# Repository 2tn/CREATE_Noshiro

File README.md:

# CREATE_Noshiro
2015年8月の能代宇宙イベントで打ち上げたCREATEのロケットに搭載したアビオニクス、「われのロガー2」のプログラム及び発注基板データ。

基板にはLPC1114とATtiny2313の二つのマイコンが搭載されている。
搭載したパーツは
- LPC1114FBD48 (メインマイコン)
- ATtiny2313-20MU (サブマイコン)
- MPU9250 (9軸センサー)
- ADXL375 (3軸大加速度センサー)
- MPL3115A2 (気圧センサー)
- BQ25071 (LiFePo充電制御チップ)
- TPS63001DRCTF4 (3.3V DC/DCコンバーター)
- LTC3872 (12V DC/DCコンバーター)
- TWE-strong (ダウンリンク用無線機器)

っていう感じ。結局のところ時間切れでATtiny2313は動かせなかった…

## われのロガー2_ATtiny2313
UARTでGPSを読んで、SPIでデータをLPC1114に渡すプログラム
## われのロガー2_LPC1114
LPC1114がGPS以外のデータ取得・SDカードへの書き込み・パラシュート開放指令を行うプログラム
## 基板
作った基板データ、Elecrowで発注した。

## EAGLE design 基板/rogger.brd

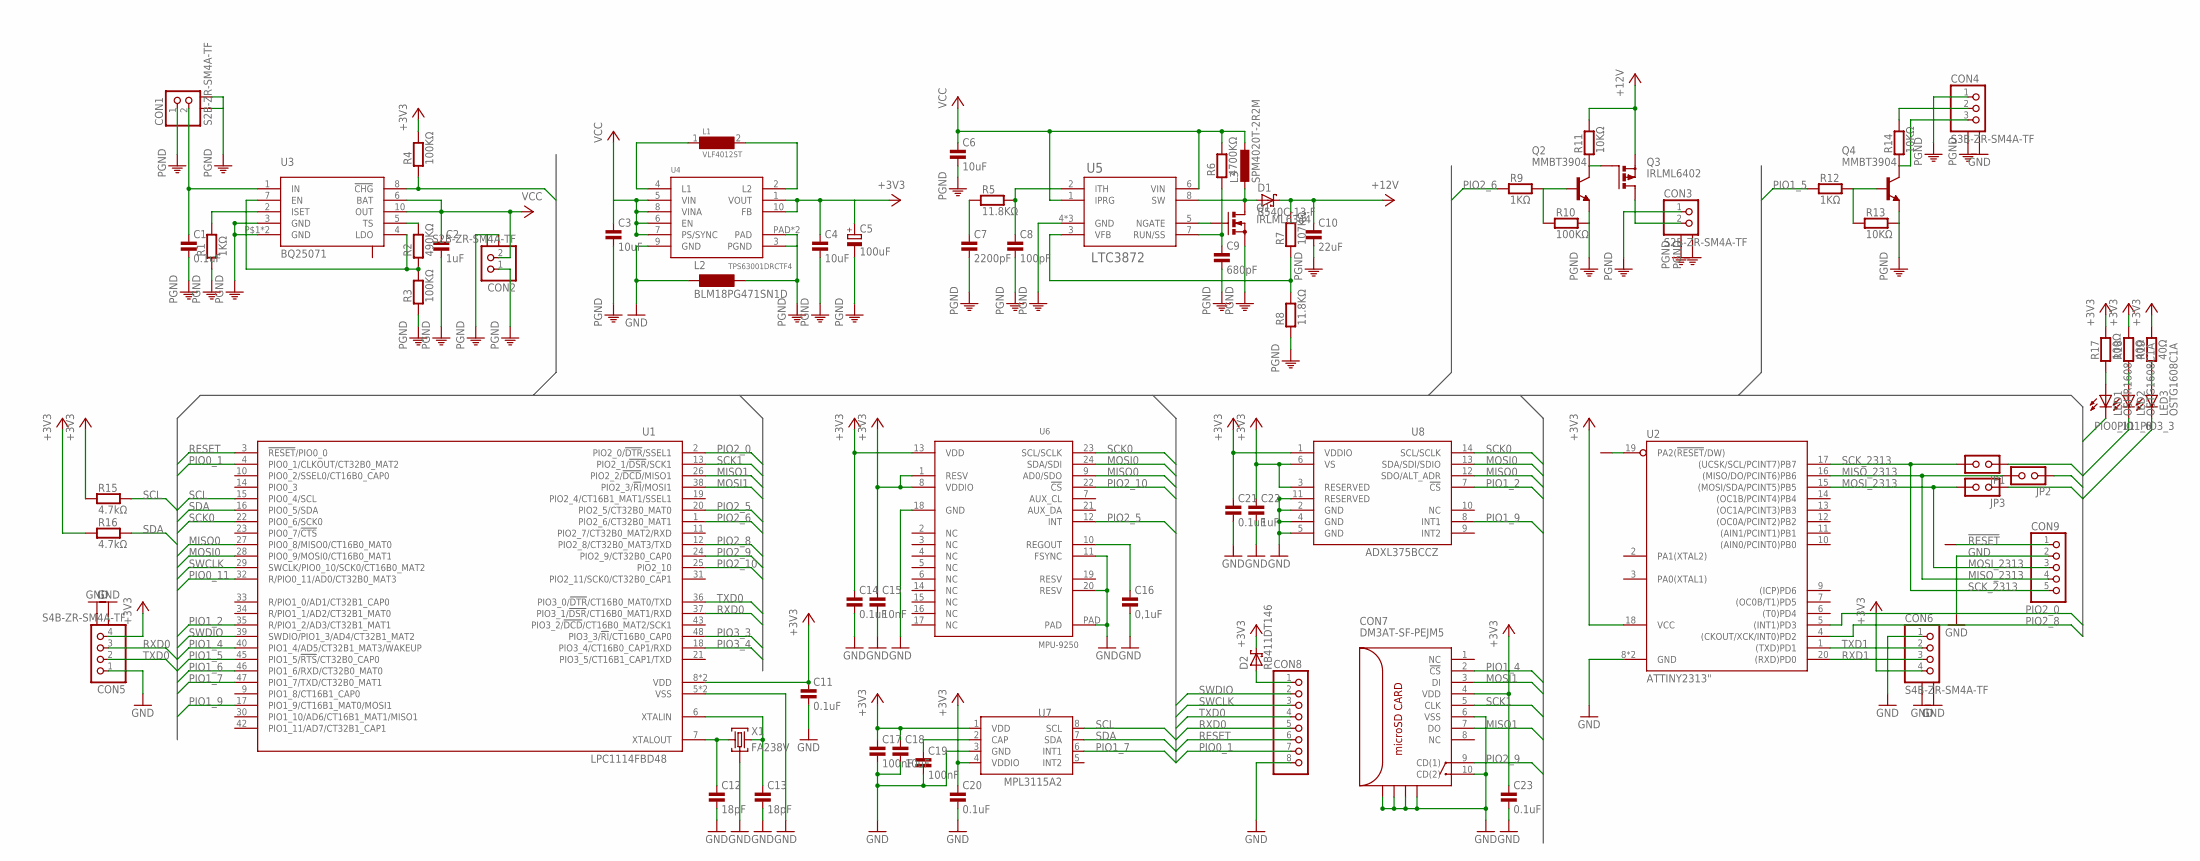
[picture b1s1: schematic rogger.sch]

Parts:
C1, C11, C14, C20, C21, C23: 0.1uF; 0603
C2, C22: 1uF; 0603
C3, C4, C6, C18: 10uF; 0603
C5: 100uF; 153CLV-0505
C7: 2200pF; 0603
C8: 100pF; 0603
C9: 680pF; 0603
C10: 22uF; 0805
C12, C13: 18pF; 0603
C15: 10nF; 0603
C16: 0,1uF; 0603
C17, C19: 100nF; 0603
CON1, CON2, CON3: S2B-ZR-SM4A-TF
CON4: S3B-ZR-SM4A-TF
CON5, CON6: S4B-ZR-SM4A-TF
CON7: DM3AT-SF-PEJM5
CON8: PINHEAD1X8; 1X8
CON9: PINHEAD1X5; 1X5
D1: B540C-13-F; SMC
D2: RB411DT146; SOT23
JP1, JP2, JP3: JUMP-2
L1: VLF4012ST
L2: BLM18PG471SN1D; 0603
L3: SPM4020T-2R2M
LED1: OSHR1608; CHIP-LED0603
LED2, LED3: OSTG1608C1A; CHIP-LED0603
Q1: IRLML6344; SOT23
Q2, Q4: MMBT3904; SOT23
Q3: IRLML6402; SOT23
R1, R9, R12: 1KΩ; 0603
R2: 490KΩ; 0603
R3, R4, R10: 100KΩ; 0603
R5, R8: 11.8KΩ; 0603
R6: 4700KΩ; 0603
R7: 107KΩ; 0603
R11, R13, R14: 10KΩ; 0603
R15, R16: 4.7kΩ; 0603
R17: 100Ω; 0603
R18, R19: 40Ω; 0603
U1: LPC1114FBD48; LQFP48
U2: ATTINY2313"; MLF20
U3: BQ25071; W-PWSON-N10
U4: TPS63001DRCTF4; S-PVSON-N10
U5: LTC3872; TSOT-23-8
U6: MPU-9250; 24QFN
U7: MPL3115A2
U8: ADXL375BCCZ; LGA-14
X1: FA238V; V66RA

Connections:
!RESET!: CON9.1, U2.19 (PA2(!RESET!/DW))
+3V3: C4.1, C5.+, C11.1, C14.1, C15.1, C17.1, C18.1, C20.1, C21.1, C22.1, C23.1, CON5.4, CON6.4, CON7.4 (VDD), D2.3 (C), R4.2, R15.1, R16.1, R17.2, R18.2, R19.2, U1.8 (VDD), U1.44 (VDD), U2.18 (VCC), U4.1 (VOUT), U4.10 (FB), U6.1 (RESV), U6.8 (VDDIO), U6.13 (VDD), U7.1 (VDD), U7.4 (VDDIO), U8.1 (VDDIO), U8.3 (RESERVED), U8.6 (VS)
+5V: CON4.2, R14.2
+12V: C10.1, D1.C, Q3.2 (S), R7.2, R11.2
GND: C11.2, C12.2, C13.2, C14.2, C15.2, C16.2, C17.2, C18.2, C19.2, C20.2, C21.2, C22.2, C23.2, CON4.PAD2, CON5.1, CON5.PAD1, CON5.PAD2, CON6.1, CON6.PAD1, CON6.PAD2, CON7.6 (VSS), CON7.10 (CD(2)), CON7.P$10, CON7.P$11, CON7.P$12, CON7.P$14, CON8.8, CON9.2, L2.1, U1.5 (VSS), U1.41 (VSS), U2.8 (GND), U2.P$1 (GND), U4.9 (GND), U6.11 (FSYNC), U6.18 (GND), U6.20 (RESV), U6.PAD, U7.3 (GND), U8.2 (GND), U8.4 (GND), U8.5 (GND), U8.11 (RESERVED), X1.P2GND (GND), X1.P4GND (GND)
MISO0: JP2.2, U1.27 (PIO0_8/MISO0/CT16B0_MAT0), U6.9 (AD0/SDO), U8.12 (SDO/ALT_ADR)
MISO1: CON7.7 (DO), U1.26 (PIO2_2/!DCD!/MISO1)
MISO_2313: CON9.4, JP2.1, U2.16 ((MISO/DO/PCINT6)PB6)
MOSI0: JP3.2, U1.28 (PIO0_9/MOSI0/CT16B0_MAT1), U6.24 (SDA/SDI), U8.13 (SDA/SDI/SDIO)
MOSI1: CON7.3 (DI), U1.38 (PIO2_3/!RI!/MOSI1)
MOSI_2313: CON9.3, JP3.1, U2.15 ((MOSI/SDA/PCINT5)PB5)
unnamed: C12.1, U1.7 (XTALOUT), X1.P1X1 (X1)
unnamed: C13.1, U1.6 (XTALIN), X1.P3X2 (X2)
unnamed: CON8.1, D2.1 (A)
unnamed: L1.1, U4.4 (L1)
unnamed: L1.2, U4.2 (L2)
unnamed: C19.1, U7.2 (CAP)
unnamed: Q1.1 (G), U5.5 (NGATE)
unnamed: D1.A, L3.P$2 (2), Q1.3 (D), U5.8 (SW)
unnamed: C16.1, U6.10 (REGOUT)
unnamed: C9.1, R6.1, U5.7 (RUN/SS)
unnamed: R1.2, U3.2 (ISET)
unnamed: R7.1, R8.2, U5.3 (VFB)
unnamed: R2.2, U3.5 (TS)
unnamed: R2.1, R3.2, U3.4 (LDO), U3.7 (EN)
unnamed: C8.1, R5.2, U5.2 (ITH)
unnamed: CON3.2, Q3.3 (D)
unnamed: C7.1, R5.1
unnamed: Q2.3 (C), Q3.1 (G), R11.1
unnamed: CON4.3, Q4.3 (C), R14.1
unnamed: Q2.1 (B), R9.2, R10.1
unnamed: Q4.1 (B), R12.2, R13.1
unnamed: LED1.A, R17.1
unnamed: C1.1, CON1.2, U3.1 (IN)
unnamed: LED2.A, R18.1
unnamed: LED3.A, R19.1
PAD: U3.9 (PAD)
PE: C1.2, C2.2, C3.2, C4.2, C5.-, C6.2, C7.2, C8.2, C9.2, C10.2, CON1.1, CON1.PAD1, CON1.PAD2, CON2.1, CON2.PAD1, CON2.PAD2, CON3.1, CON3.PAD1, CON3.PAD2, CON4.1, CON4.PAD1, L2.2, Q1.2 (S), Q2.2 (E), Q4.2 (E), R1.1, R3.1, R8.1, R10.2, R13.2, U3.3 (GND), U3.P$1 (GND), U3.PAD (GND), U4.3 (PGND), U4.PAD, U4.PAD@1 (PAD), U5.4 (GND), U5.P$1 (GND), U5.P$2 (GND)
PIO0_1: CON8.7, U1.4 (PIO0_1/CLKOUT/CT32B0_MAT2)
PIO0_11: LED1.C, U1.32 (R/PIO0_11/AD0/CT32B0_MAT3)
PIO1_2: U1.35 (R/PIO1_2/AD3/CT32B1_MAT1), U8.7 (!CS!)
PIO1_4: CON7.2 (!CS!), U1.40 (PIO1_4/AD5/CT32B1_MAT3/WAKEUP)
PIO1_5: R12.1, U1.45 (PIO1_5/!RTS!/CT32B0_CAP0)
PIO1_6: LED2.C, U1.46 (PIO1_6/RXD/CT32B0_MAT0)
PIO1_7: U1.47 (PIO1_7/TXD/CT32B0_MAT1), U7.6 (INT1)
PIO1_9: U1.17 (PIO1_9/CT16B1_MAT0/MOSI1), U8.8 (INT1)
PIO2_0: U1.2 (PIO2_0/!DTR!/SSEL1), U2.5 ((INT1)PD3)
PIO2_5: U1.20 (PIO2_5/CT32B0_MAT0), U6.12 (INT)
PIO2_6: R9.1, U1.1 (PIO2_6/CT32B0_MAT1)
PIO2_8: U1.12 (PIO2_8/CT32B0_MAT3/TXD), U2.4 ((CKOUT/XCK/INT0)PD2)
PIO2_9: CON7.9 (CD(1)), U1.24 (PIO2_9/CT32B0_CAP0)
PIO2_10: U1.25 (PIO2_10), U6.22 (!CS!)
PIO3_3: LED3.C, U1.48 (PIO3_3/!RI!/CT16B0_CAP0)
PIO3_4: R4.1, U1.18 (PIO3_4/CT16B0_CAP1/RXD), U3.8 (!CHG!)
RESET: CON8.6, U1.3 (!RESET!/PIO0_0)
RXD0: CON5.3, CON8.5, U1.37 (PIO3_1/!DSR!/CT16B0_MAT1/RXD)
RXD1: CON6.3, U2.20 ((RXD)PD0)
SCK0: JP1.2, U1.22 (PIO0_6/SCK0), U6.23 (SCL/SCLK), U8.14 (SCL/SCLK)
SCK1: CON7.5 (CLK), U1.13 (PIO2_1/!DSR!/SCK1)
SCK_2313: CON9.5, JP1.1, U2.17 ((UCSK/SCL/PCINT7)PB7)
SCL: R15.2, U1.15 (PIO0_4/SCL), U7.8 (SCL)
SDA: R16.2, U1.16 (PIO0_5/SDA), U7.7 (SDA)
SWCLK: CON8.3, U1.29 (SWCLK/PIO0_10/SCK0/CT16B0_MAT2)
SWDIO: CON8.2, U1.39 (SWDIO/PIO1_3/AD4/CT32B1_MAT2)
TXD0: CON5.2, CON8.4, U1.36 (PIO3_0/!DTR!/CT16B0_MAT0/TXD)
TXD1: CON6.2, U2.1 ((TXD)PD1)
VCC: C2.1, C3.1, C6.1, CON2.2, L3.P$1 (1), R6.2, U3.6 (BAT), U3.10 (OUT), U4.5 (VIN), U4.6 (EN), U4.7 (PS/SYNC), U4.8 (VINA), U5.1 (IPRG), U5.6 (VIN)

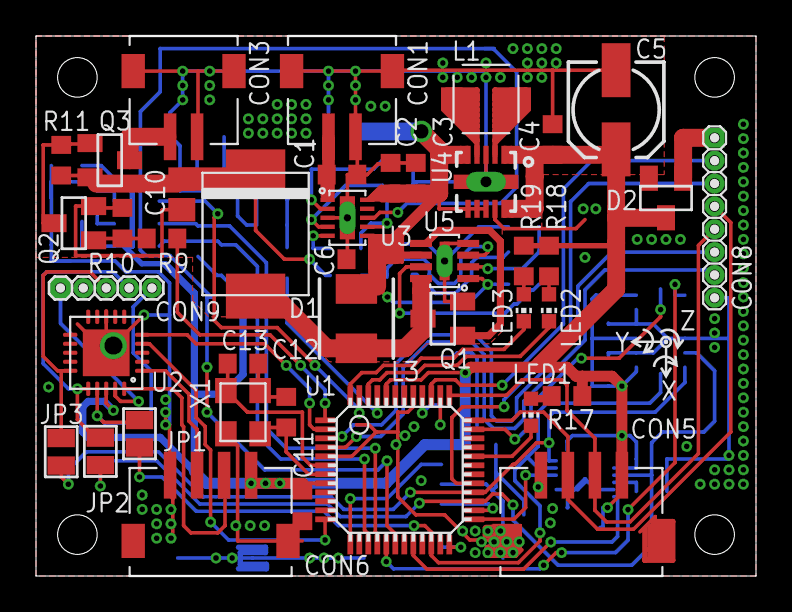
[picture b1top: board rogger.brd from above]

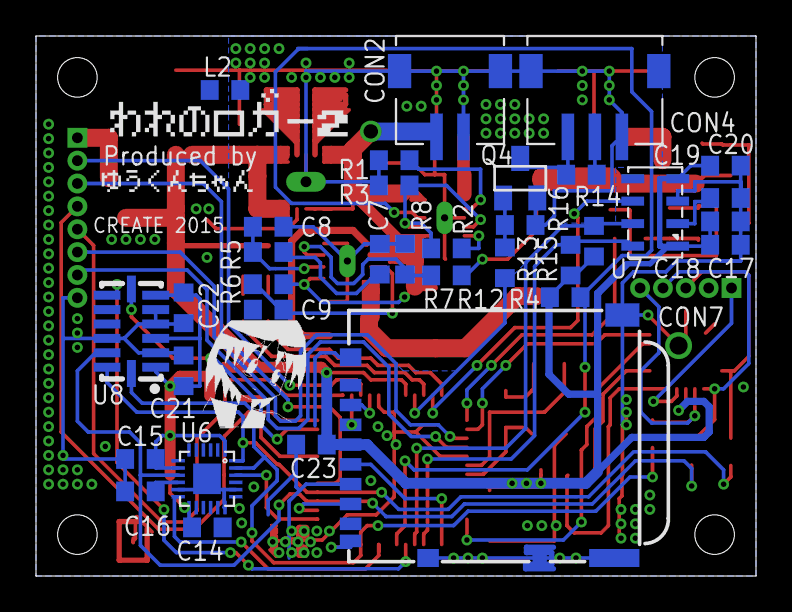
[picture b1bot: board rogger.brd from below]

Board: 2 copper layers, 40.0 x 30.0 mm, 76 parts (34 on the bottom side), 66 nets.

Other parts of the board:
U$1: DIRECTION

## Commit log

2018-05-12 マイコン名違った…
